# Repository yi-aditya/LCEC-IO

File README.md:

# LCEC-IO

Industrial EtherCAT slave I/O board: STM32F405VGT6 + LAN9252, 8 digital inputs, 12 MPG selector inputs, MPG encoder, 8 pluggable relay outputs, 2 × 0–10 V analog outputs. Designed in KiCad 10 with Claude Code.

- Specification: [docs/plan.md](docs/plan.md)
- Rules for Claude Code: [CLAUDE.md](CLAUDE.md)
- Cloud environment setup script: [scripts/cloud-setup.sh](scripts/cloud-setup.sh)

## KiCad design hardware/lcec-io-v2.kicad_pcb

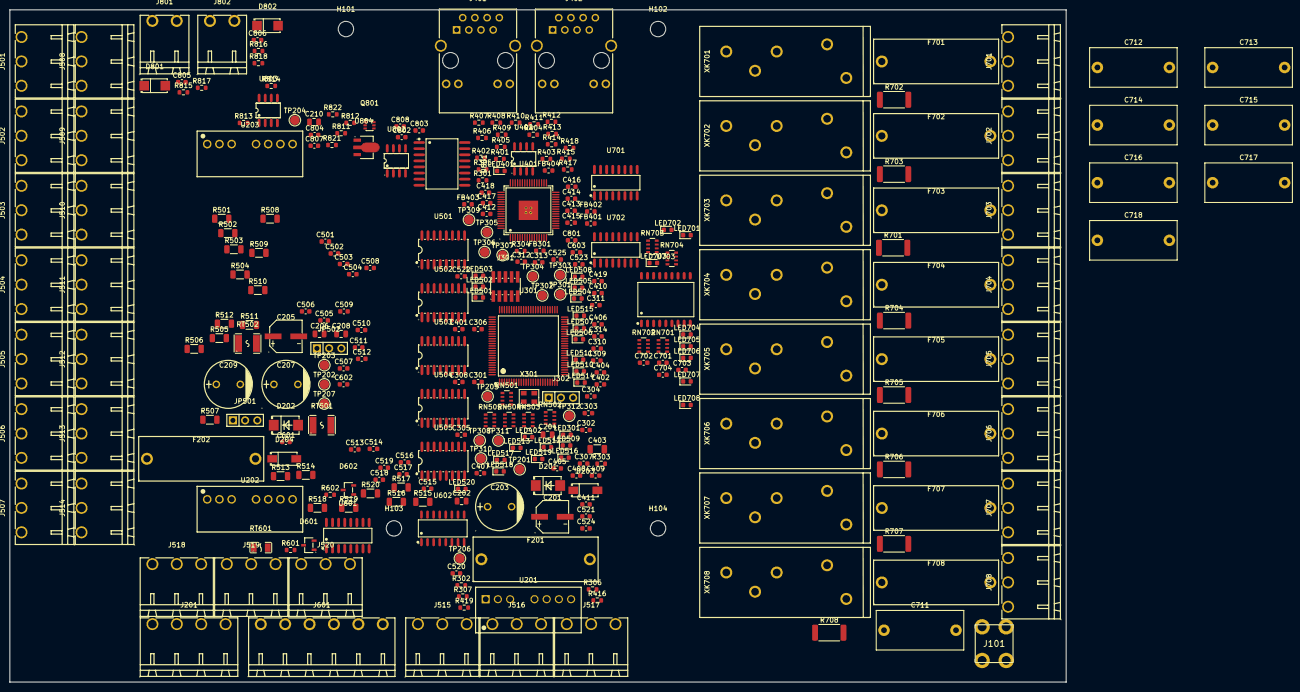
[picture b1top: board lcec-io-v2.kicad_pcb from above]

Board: 4 copper layers, 220.0 x 140.0 mm, 315 parts (0 on the bottom side), 249 nets, no tracks yet.

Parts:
C201, C205: 47uF 50V; CAP-SMD_BD6.3-L6.6-W6.6-LS7.2-FD
C202, C206: 1uF 50V; C_0805_2012Metric
C203, C207, C209: 100uF 100V; CAP-TH_BD10.0-P5.00-D0.6-FD
C204, C208, C210: 22uF 25V; C_0805_2012Metric
C301, C302, C303, C304, C305, C306, C307, C310, C313, C314, C404, C405, C406, C407, C408, C409, C410, C411, C412, C415, C416, C417, C418, C419, C521, C522, C523, C524, C525, C601, C602, C603, C701, C702, C703, C704, C801, C802, C803, C804: 100nF; C_0603_1608Metric
C308: 4.7uF; C_0603_1608Metric
C309, C413, C807, C808: 1uF; C_0603_1608Metric
C311, C312: 2.2uF; C_0603_1608Metric
C401, C402: 22nF 50V; C_0603_1608Metric
C403: 1nF 2kV; C_1206_3216Metric
C414: 470pF; C_0603_1608Metric
C501, C502, C503, C504, C505, C506, C507, C508, C509, C510, C511, C512, C513, C514, C515, C516, C517, C518, C519, C520, C805, C806: 10nF; C_0603_1608Metric
C711, C712, C713, C714, C715, C716, C717, C718: 47nF X2; C_Rect_L18.0mm_W8.0mm_P15.00mm_FKS3_FKP3
D201, D202: SMBJ30A; SMB_L4.4-W3.6-LS5.4-RD
D203, D204: SS54; SMA_L4.4-W2.8-LS5.4-R-RD
D601, D602: PSM712; SOT-23-3_L3.0-W1.7-P0.95-LS2.9-BR
D801, D802: SMAJ15A; SMA_L4.3-W2.6-LS5.2-RD
F201: 1 A 5x20; 64600001003
F202: 3 A 5x20; 64600001003
F701, F702, F703, F704, F705, F706, F707, F708: T5A 5x20; 64600001003
FB301: 600R@100MHz; L_0603_1608Metric
FB401, FB402, FB403, FB404: 220R@100MHz; L_0603_1608Metric
H101, H102, H103, H104: M3; MountingHole_3.2mm_M3
J101: PE; Keystone_7770_M3_PCB_Terminal
J201: 24 V entry; CONN-TH_4P-P5.08_KF2EDGR-5.08-4P
J301: SWD 2x5 1.27 mm; HDR-SMD_10P-P1.27-V-M-R2-C5-LS5.3
J302: USART2; HDR-TH_3P-P2.54-V-M_PZ254V-11-03P
J401, J402: HY911105AE; RJ45-TH_HR911105A
J501, J502, J503, J504, J505, J506, J507, J508, J509, J510, J511, J512, J513, J514, J515, J516, J517, J518, J519, J520: IN; CONN-TH_3P-P5.08_KF2EDGR-5.08-3P
J601: MPG; CONN-TH_6P-P5.08_KF2EDGR-5.08-6P
J701: DO1; CONN-TH_3P-P5.08_KF2EDGR-5.08-3P
J702: DO2; CONN-TH_3P-P5.08_KF2EDGR-5.08-3P
J703: DO3; CONN-TH_3P-P5.08_KF2EDGR-5.08-3P
J704: DO4; CONN-TH_3P-P5.08_KF2EDGR-5.08-3P
J705: DO5; CONN-TH_3P-P5.08_KF2EDGR-5.08-3P
J706: DO6; CONN-TH_3P-P5.08_KF2EDGR-5.08-3P
J707: DO7; CONN-TH_3P-P5.08_KF2EDGR-5.08-3P
J708: DO8; CONN-TH_3P-P5.08_KF2EDGR-5.08-3P
J801: AO1; CONN-TH_2P-P5.08_KF2EDGR-5.08-2P
J802: AO2; CONN-TH_2P-P5.08_KF2EDGR-5.08-2P
JP501, JP502: COM; HDR-TH_3P-P2.54-V-M_PZ254V-11-03P
LED301: heartbeat; LED_0603_1608Metric
LED401: RUN; LED_0603_1608Metric
LED402: ERR; LED_0603_1608Metric
LED501, LED502, LED503, LED504, LED505, LED506, LED507, LED508, LED509, LED510, LED511, LED512, LED513, LED514, LED515, LED516, LED517, LED518, LED519, LED520: IN; LED_0603_1608Metric
LED701, LED702, LED703, LED704, LED705, LED706, LED707, LED708: ON; LED_0603_1608Metric
Q801: 2N7002DW; SOT-363_L2.0-W1.3-P0.65-LS2.1-TL
R301, R302, R304, R305, R402, R403, R405: 10k; R_0603_1608Metric
R303, R401, R404, R406, R419, R811, R812: 1k; R_0603_1608Metric
R306, R307: 22R; R_0603_1608Metric
R407, R408, R409, R410, R411, R412, R413, R414: 49.9R; R_0603_1608Metric
R415: 12.1k 1%; R_0603_1608Metric
R416: 1M; R_0603_1608Metric
R417, R418: 4.7k; R_0603_1608Metric
R501, R502, R503, R504, R505, R506, R507, R508, R509, R510, R511, R512, R513, R514, R515, R516, R517, R518, R519, R520: 4.7k; R_1206_3216Metric
R601, R602: 120R; R_0603_1608Metric
R701, R702, R703, R704, R705, R706, R707, R708: 100R; R_2512_6332Metric
R813, R814: 10.0k 0.1%; R_0603_1608Metric
R815, R816: 100R; R_0603_1608Metric
R817, R818: 14.7k 0.1%; R_0603_1608Metric
R821, R822: 100k; R_0603_1608Metric
RN501, RN502, RN503, RN504, RN505: 4x1k; R_Array_Convex_4x0603
RN701, RN702: 4x22k; R_Array_Convex_4x0603
RN703, RN704: 4x100k; R_Array_Convex_4x0603
RT501, RT502: 0.5A PTC; F1812
RT601: 0.25A PTC; F1206
TP201: +24V_LOGIC; TestPoint_Pad_D2.0mm
TP202: +24V_IO; TestPoint_Pad_D2.0mm
TP203: +5V_IO; TestPoint_Pad_D2.0mm
TP204: +15V_A; TestPoint_Pad_D2.0mm
TP205: +3V3; TestPoint_Pad_D2.0mm
TP206: 0V_LOGIC; TestPoint_Pad_D2.0mm
TP207: 0V_IO; TestPoint_Pad_D2.0mm
TP301: ESC_SCK; TestPoint_Pad_D2.0mm
TP302: ESC_MISO; TestPoint_Pad_D2.0mm
TP303: ESC_MOSI; TestPoint_Pad_D2.0mm
TP304: ESC_CS; TestPoint_Pad_D2.0mm
TP305: DAC_SCK; TestPoint_Pad_D2.0mm
TP306: DAC_MOSI; TestPoint_Pad_D2.0mm
TP307: DAC_CS; TestPoint_Pad_D2.0mm
TP308: RELAY_OE; TestPoint_Pad_D2.0mm
TP309: AO_CLAMP; TestPoint_Pad_D2.0mm
TP310: MPG_A; TestPoint_Pad_D2.0mm
TP311: MPG_B; TestPoint_Pad_D2.0mm
TP312: PH1_TP; TestPoint_Pad_D2.0mm
U201: URB2403S-6WR3; PWRM-TH_URBXXXXS-6WR3_1
U202: URB2405S-6WR3; PWRM-TH_YLPTEC_URXXXXXS-6WR3
U203: URB2415S-6WR3; PWRM-TH_URBXXXXS-6WR3
U301: STM32F405VGT6; LQFP-100_L14.0-W14.0-P0.50-LS16.0-BL
U401: LAN9252I/PT; TQFP-64_L10.0-W10.0-P0.50-LS12.0-BL-EP
U402: 24LC32AT-I/SN; SOIC-8_L4.9-W3.9-P1.27-LS6.0-BL
U501, U502, U503, U504, U505: TLP290-4; SOP-16_L10.3-W4.4-P1.27-LS7.0-BL
U601: AM26LS32A; SOIC-16_L9.9-W3.9-P1.27-LS6.0-BL
U602: CA-IS3742LN; SOP-16_L10.0-W3.9-P1.27-LS6.0-BL
U701, U702: CA-IS3740LN; SOIC-16_L9.9-W3.9-P1.27-LS6.0-BL
U703: ULN2803A; SOP-18_L11.4-W7.6-P1.27-LS10.6-BL
U801: CA-IS3740HW; SOIC-16_L10.3-W7.5-P1.27-LS10.3-BL
U802: MCP4822-E/SN; SOIC-8_L4.9-W3.9-P1.27-LS6.0-BL
U803: LM2904; SOIC-8_L4.9-W3.9-P1.27-LS6.0-BL
U804: L78L05; SOT-89-3_L4.5-W2.5-P1.50-LS4.2-TL
X301: 25 MHz; OSC-SMD_4P-L3.2-W2.5-BL_KYOCERA_KC3225A
XK701, XK702, XK703, XK704, XK705, XK706, XK707, XK708: P2R-05P; RELAY-TH_P2R-05P

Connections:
0V_IO: C205.2, C206.2, C207.2, C208.2, C209.2, C601.2, C602.2, C702.2, C704.2, D202.2, D601.3, D602.3, J201.4, J501.3, J502.3, J503.3, J504.3, J505.3, J506.3, J507.3, J508.3, J509.3, J510.3, J511.3, J512.3, J513.3, J514.3, J515.3, J516.3, J517.3, J518.3, J519.3, J520.3, J601.2, JP501.3, JP502.3, RN703.1, RN703.2, RN703.3, RN703.4, RN704.1, RN704.2, RN704.3, RN704.4, TP207.1, U202.1, U202.7, U203.1, U601.8, U601.9, U601.10, U601.12, U601.14, U601.15, U602.9, U602.15, U701.9, U701.15, U702.9, U702.15, U703.9
0V_LOGIC: C201.2, C202.2, C203.2, D201.2, J201.2, TP206.1, U201.1
+3V3: C204.1, C301.1, C302.1, C303.1, C304.1, C305.1, C306.1, C307.1, C308.1, C314.1, C404.1, C405.1, C406.1, C407.1, C408.1, C409.1, C419.1, C521.1, C522.1, C523.1, C524.1, C525.1, C603.1, C701.1, C703.1, C801.1, FB301.1, FB401.1, FB402.1, FB403.1, J301.1, R304.1, R305.1, R401.1, R402.1, R417.1, R418.1, RN501.1, RN501.2, RN501.3, RN501.4, RN502.1, RN502.2, RN502.3, RN502.4, RN503.1, RN503.2, RN503.3, RN503.4, RN504.1, RN504.2, RN504.3, RN504.4, RN505.1, RN505.2, RN505.3, RN505.4, TP205.1, U201.6, U301.6, U301.11, U301.19, U301.28, U301.50, U301.75, U301.100, U401.5, U401.7, U401.14, U401.20, U401.32, U401.37, U401.47, U402.8, U602.1, U602.7, U701.1, U702.1, U801.1, X301.1, X301.4
+3V3_BIAS: C412.1, FB403.2, U401.58
+3V3_TXRX1: C401.1, C410.1, FB401.2, J401.4, J401.5, R407.1, R408.1, R409.1, R410.1, U401.51
+3V3_TXRX2: C402.1, C411.1, FB402.2, J402.4, J402.5, R411.1, R412.1, R413.1, R414.1, U401.64
+5V_A: C802.1, C803.1, C808.1, U801.10, U801.16, U802.1, U804.1
+5V_IO: C208.1, C601.1, C602.1, C702.1, C704.1, RT601.2, TP203.1, U202.6, U601.4, U601.16, U602.10, U602.16, U701.16, U702.16
+15V_A: C210.1, C804.1, C807.1, TP204.1, U203.6, U803.8, U804.3
+24V_IO: C205.1, C206.1, C207.1, C209.1, D202.1, D204.2, JP501.1, JP502.1, RN701.5, RN701.6, RN701.7, RN701.8, RN702.5, RN702.6, RN702.7, RN702.8, RT501.1, RT502.1, TP202.1, U202.2, U203.2, U703.10, XK701.1, XK702.1, XK703.1, XK704.1, XK705.1, XK706.1, XK707.1, XK708.1
+24V_LOGIC: C201.1, C202.1, C203.1, D201.1, D203.2, TP201.1, U201.2
/Analog/AO1_P: Q801.3, R811.2, R821.1, U803.3
/Analog/AO2_P: Q801.6, R812.2, R822.1, U803.5
/Analog/CLAMP_A: Q801.2, Q801.5, U801.11
/Analog/CS_A: U801.12, U802.2
/Analog/DAC_A: R811.1, U802.8
/Analog/DAC_B: R812.1, U802.6
/Analog/SCK_A: U801.14, U802.3
/Analog/SDI_A: U801.13, U802.4
/EtherCAT/CLK_ESC: R307.2, U401.1
/EtherCAT/EESCL: R417.2, U401.43, U402.6
/EtherCAT/EESDA: R418.2, U401.42, U402.5
/EtherCAT/ERR_LED: R419.1, U301.84
/EtherCAT/ESC_IRQ: U301.33, U401.44
/EtherCAT/ESC_RST: R304.2, U301.34, U401.11
/EtherCAT/ESC_SYNC0: U301.23, U401.34
/EtherCAT/ESC_SYNC1: U301.7, U401.18
/EtherCAT/LNK_ACT0: J401.9, R406.1
/EtherCAT/LNK_ACT1: J402.9, R404.1
/EtherCAT/SHIELD: C403.1, J401.8, J401.SH1, J401.SH2, J402.8, J402.SH1, J402.SH2, R416.1
/EtherCAT/VDD12TX: C417.1, C418.1, FB404.2, U401.56, U401.59
/EtherCAT/VDDCR: C413.1, C414.1, C415.1, C416.1, FB404.1, U401.6, U401.24, U401.38
/Inputs/COM_DI: C501.2, C502.2, C503.2, C504.2, C505.2, C506.2, C507.2, C508.2, JP501.2, U501.2, U501.4, U501.6, U501.8, U502.2, U502.4, U502.6, U502.8
/Inputs/COM_SEL: C509.2, C510.2, C511.2, C512.2, C513.2, C514.2, C515.2, C516.2, C517.2, C518.2, C519.2, C520.2, JP502.2, U503.2, U503.4, U503.6, U503.8, U504.2, U504.4, U504.6, U504.8, U505.2, U505.4, U505.6, U505.8
/Inputs/DI1: LED501.1, U301.15, U501.16
/Inputs/DI1-4/LA1: LED501.2, RN501.5
/Inputs/DI1-4/LA2: LED502.2, RN501.6
/Inputs/DI1-4/LA3: LED503.2, RN501.7
/Inputs/DI1-4/LA4: LED504.2, RN501.8
/Inputs/DI2: LED502.1, U301.16, U501.14
/Inputs/DI3: LED503.1, U301.17, U501.12
/Inputs/DI4: LED504.1, U301.18, U501.10
/Inputs/DI5: LED505.1, U301.63, U502.16
/Inputs/DI5-8/LA1: LED505.2, RN502.5
/Inputs/DI5-8/LA2: LED506.2, RN502.6
/Inputs/DI5-8/LA3: LED507.2, RN502.7
/Inputs/DI5-8/LA4: LED508.2, RN502.8
/Inputs/DI6: LED506.1, U301.64, U502.14
/Inputs/DI7: LED507.1, U301.65, U502.12
/Inputs/DI8: LED508.1, U301.66, U502.10
/Inputs/SEL1: LED509.1, U301.35, U503.16
/Inputs/SEL1-4/LA1: LED509.2, RN503.5
/Inputs/SEL1-4/LA2: LED510.2, RN503.6
/Inputs/SEL1-4/LA3: LED511.2, RN503.7
/Inputs/SEL1-4/LA4: LED512.2, RN503.8
/Inputs/SEL2: LED510.1, U301.36, U503.14
/Inputs/SEL3: LED511.1, U301.37, U503.12
/Inputs/SEL4: LED512.1, U301.95, U503.10
/Inputs/SEL5: LED513.1, U301.96, U504.16
/Inputs/SEL5-8/LA1: LED513.2, RN504.5
/Inputs/SEL5-8/LA2: LED514.2, RN504.6
/Inputs/SEL5-8/LA3: LED515.2, RN504.7
/Inputs/SEL5-8/LA4: LED516.2, RN504.8
/Inputs/SEL6: LED514.1, U301.47, U504.14
/Inputs/SEL7: LED515.1, U301.48, U504.12
/Inputs/SEL8: LED516.1, U301.77, U504.10
/Inputs/SEL9: LED517.1, U301.92, U505.16
/Inputs/SEL9-12/LA1: LED517.2, RN505.5
/Inputs/SEL9-12/LA2: LED518.2, RN505.6
/Inputs/SEL9-12/LA3: LED519.2, RN505.7
/Inputs/SEL9-12/LA4: LED520.2, RN505.8
/Inputs/SEL10: LED518.1, U301.93, U505.14
/Inputs/SEL11: LED519.1, U301.8, U505.12
/Inputs/SEL12: LED520.1, U301.9, U505.10
/Inputs/SENSE_DI: J501.1, J502.1, J503.1, J504.1, J505.1, J506.1, J507.1, J508.1, RT501.2
/Inputs/SENSE_SEL: J509.1, J510.1, J511.1, J512.1, J513.1, J514.1, J515.1, J516.1, J517.1, J518.1, J519.1, J520.1, RT502.2
/MCU/AO_CLAMP: R305.2, TP309.1, U301.53, U801.6
/MCU/BOOT0: R301.1, U301.94
/MCU/CLK_MCU: R306.2, U301.12
/MCU/DAC_CS: TP307.1, U301.51, U801.5
/MCU/DAC_MOSI: TP306.1, U301.54, U801.4
/MCU/DAC_SCK: TP305.1, U301.52, U801.3
/MCU/DO1: U301.67, U701.3
/MCU/DO2: U301.68, U701.4
/MCU/DO3: U301.69, U701.5
/MCU/DO4: U301.70, U701.6
/MCU/DO5: U301.71, U702.3
/MCU/DO6: U301.78, U702.4
/MCU/DO7: U301.79, U702.5
/MCU/DO8: U301.80, U702.6
/MCU/ESC_CS: TP304.1, U301.29, U401.50
/MCU/ESC_MISO: TP302.1, U301.31, U401.13
/MCU/ESC_MOSI: TP303.1, U301.32, U401.17
/MCU/ESC_SCK: TP301.1, U301.30, U401.19
/MCU/HB_LED: R303.1, U301.24
/MCU/MPG_A: TP310.1, U301.90, U602.5
/MCU/MPG_B: TP311.1, U301.91, U602.6
/MCU/NRST: C313.1, J301.10, U301.14
/MCU/PH1_TP: TP312.1, U301.13
/MCU/RELAY_OE: R302.1, TP308.1, U301.83, U602.3
/MCU/SWCLK: J301.4, U301.76
/MCU/SWDIO: J301.2, U301.72
/MCU/SWO: J301.6, U301.89
/MCU/UART2_RX: J302.2, U301.26
/MCU/UART2_TX: J302.1, U301.25
/MCU/VDDA: C309.1, C310.1, FB301.2, U301.21, U301.22
/MPG/ENC_A_N: D601.2, J601.4, R601.2, U601.1
/MPG/ENC_A_P: D601.1, J601.3, R601.1, U601.2
/MPG/ENC_A_R: U601.3, U602.12
/MPG/ENC_B_N: D602.2, J601.6, R602.2, U601.7
/MPG/ENC_B_P: D602.1, J601.5, R602.1, U601.6
/MPG/ENC_B_R: U601.5, U602.11
/OE_FIELD: U602.14, U701.10, U702.10
/Power/24V_IO_IN: F202.1, J201.3
/Power/24V_LOGIC_IN: F201.1, J201.1
/Relays/DRV1: LED701.1, U703.18, XK701.5
/Relays/DRV2: LED702.1, U703.17, XK702.5
/Relays/DRV3: LED703.1, U703.16, XK703.5
/Relays/DRV4: LED704.1, U703.15, XK704.5
/Relays/DRV5: LED705.1, U703.14, XK705.5
/Relays/DRV6: LED706.1, U703.13, XK706.5
/Relays/DRV7: LED707.1, U703.12, XK707.5
/Relays/DRV8: LED708.1, U703.11, XK708.5
/Relays/IN1: RN703.5, U701.14, U703.1
/Relays/IN2: RN703.6, U701.13, U703.2
/Relays/IN3: RN703.7, U701.12, U703.3
/Relays/IN4: RN703.8, U701.11, U703.4
/Relays/IN5: RN704.5, U702.14, U703.5
/Relays/IN6: RN704.6, U702.13, U703.6
/Relays/IN7: RN704.7, U702.12, U703.7
/Relays/IN8: RN704.8, U702.11, U703.8
/Relays/LR1: LED701.2, RN701.4
/Relays/LR2: LED702.2, RN701.3
/Relays/LR3: LED703.2, RN701.2
/Relays/LR4: LED704.2, RN701.1
/Relays/LR5: LED705.2, RN702.4
/Relays/LR6: LED706.2, RN702.3
/Relays/LR7: LED707.2, RN702.2
/Relays/LR8: LED708.2, RN702.1
AGND: C210.2, C802.2, C803.2, C804.2, C805.2, C806.2, C807.2, C808.2, D801.2, D802.2, J801.2, J802.2, Q801.1, Q801.4, R813.2, R814.2, R821.2, R822.2, U203.7, U801.9, U801.15, U802.5, U802.7, U803.4, U804.2
GND_L: C204.2, C301.2, C302.2, C303.2, C304.2, C305.2, C306.2, C307.2, C308.2, C309.2, C310.2, C311.2, C312.2, C313.2, C314.2, C401.2, C402.2, C404.2, C405.2, C406.2, C407.2, C408.2, C409.2, C410.2, C411.2, C412.2, C413.2, C414.2, C415.2, C416.2, C417.2, C418.2, C419.2, C521.2, C522.2, C523.2, C524.2, C525.2, C603.2, C701.2, C703.2, C801.2, J301.3, J301.5, J301.9, J302.3, J401.10, J402.10, LED301.1, LED402.1, R301.2, R302.2, R403.2, R405.2, R415.2, U201.7, U301.10, U301.20, U301.27, U301.74, U301.99, U401.4, U401.8, U401.9, U401.10, U401.41, U401.65, U402.1, U402.2, U402.3, U402.4, U402.7, U501.9, U501.11, U501.13, U501.15, U502.9, U502.11, U502.13, U502.15, U503.9, U503.11, U503.13, U503.15, U504.9, U504.11, U504.13, U504.15, U505.9, U505.11, U505.13, U505.15, U602.2, U602.4, U602.8, U701.2, U701.8, U702.2, U702.8, U801.2, U801.8, X301.2
unnamed: C711.1, R701.2
unnamed: C712.1, R702.2
unnamed: C713.1, R703.2
unnamed: C714.1, R704.2
unnamed: C715.1, R705.2
unnamed: C716.1, R706.2
unnamed: C717.1, R707.2
unnamed: C718.1, R708.2
unnamed: D203.1, F201.2
unnamed: D204.1, F202.2
unnamed: C805.1, D801.1, J801.1, R815.2, R817.2
unnamed: C806.1, D802.1, J802.1, R816.2, R818.2
unnamed: F701.2, J701.1
unnamed: F702.2, J702.1
unnamed: F703.2, J703.1
unnamed: F704.2, J704.1
unnamed: F705.2, J705.1
unnamed: F706.2, J706.1
unnamed: F707.2, J707.1
unnamed: F708.2, J708.1
unnamed: J401.3, R409.2, U401.55
unnamed: J401.6, R410.2, U401.54
unnamed: J401.1, R407.2, U401.53
unnamed: J401.2, R408.2, U401.52
unnamed: J402.3, R413.2, U401.60
unnamed: J402.6, R414.2, U401.61
unnamed: J402.1, R411.2, U401.62
unnamed: J402.2, R412.2, U401.63
unnamed: J501.2, R501.1
unnamed: J502.2, R502.1
unnamed: J503.2, R503.1
unnamed: J504.2, R504.1
unnamed: J505.2, R505.1
unnamed: J506.2, R506.1
unnamed: J507.2, R507.1
unnamed: J508.2, R508.1
unnamed: J509.2, R509.1
unnamed: J510.2, R510.1
unnamed: J511.2, R511.1
unnamed: J512.2, R512.1
unnamed: J513.2, R513.1
unnamed: J514.2, R514.1
unnamed: J515.2, R515.1
unnamed: J516.2, R516.1
unnamed: J517.2, R517.1
unnamed: J518.2, R518.1
unnamed: J519.2, R519.1
unnamed: J520.2, R520.1
unnamed: J601.1, RT601.1
unnamed: LED301.2, R303.2
unnamed: LED401.2, R401.2
unnamed: LED401.1, R402.2, U401.45
unnamed: LED402.2, R419.2
unnamed: C311.1, U301.49
unnamed: C312.1, U301.73
unnamed: R405.1, R406.2, U401.48
unnamed: R403.1, R404.2, U401.46
unnamed: R415.1, U401.57
unnamed: C501.1, R501.2, U501.1
unnamed: C502.1, R502.2, U501.3
unnamed: C503.1, R503.2, U501.5
unnamed: C504.1, R504.2, U501.7
unnamed: C505.1, R505.2, U502.1
unnamed: C506.1, R506.2, U502.3
unnamed: C507.1, R507.2, U502.5
unnamed: C508.1, R508.2, U502.7
unnamed: C509.1, R509.2, U503.1
unnamed: C510.1, R510.2, U503.3
unnamed: C511.1, R511.2, U503.5
unnamed: C512.1, R512.2, U503.7
unnamed: C513.1, R513.2, U504.1
unnamed: C514.1, R514.2, U504.3
unnamed: C515.1, R515.2, U504.5
unnamed: C516.1, R516.2, U504.7
unnamed: C517.1, R517.2, U505.1
unnamed: C518.1, R518.2, U505.3
unnamed: C519.1, R519.2, U505.5
unnamed: C520.1, R520.2, U505.7
unnamed: R813.1, R817.1, U803.2
unnamed: R815.1, U803.1
unnamed: R814.1, R818.1, U803.6
unnamed: R816.1, U803.7
unnamed: R306.1, R307.1, X301.3
unnamed: F701.1, R701.1, XK701.2
unnamed: J701.3, XK701.4
unnamed: C711.2, J701.2, XK701.3
unnamed: F702.1, R702.1, XK702.2
unnamed: J702.3, XK702.4
unnamed: C712.2, J702.2, XK702.3
unnamed: F703.1, R703.1, XK703.2
unnamed: J703.3, XK703.4
unnamed: C713.2, J703.2, XK703.3
unnamed: F704.1, R704.1, XK704.2
unnamed: J704.3, XK704.4
unnamed: C714.2, J704.2, XK704.3
unnamed: F705.1, R705.1, XK705.2
unnamed: J705.3, XK705.4
unnamed: C715.2, J705.2, XK705.3
unnamed: F706.1, R706.1, XK706.2
unnamed: J706.3, XK706.4
unnamed: C716.2, J706.2, XK706.3
unnamed: F707.1, R707.1, XK707.2
unnamed: J707.3, XK707.4
unnamed: C717.2, J707.2, XK707.3
unnamed: F708.1, R708.1, XK708.2
unnamed: J708.3, XK708.4
unnamed: C718.2, J708.2, XK708.3
PE: C403.2, J101.1, R416.2

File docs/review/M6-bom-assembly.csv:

Refs,Qty,Value,Footprint,LCSC,MPN,Manufacturer
"C201,C205",2,47uF 50V,lcsc:CAP-SMD_BD6.3-L6.6-W6.6-LS7.2-FD,C970679,RVT1H470M0607 47UF 50V,DMBJ
"C202,C206",2,1uF 50V,Capacitor_SMD:C_0805_2012Metric,C91185,CC0805KKX7R9BB105,YAGEO
"C203,C207,C209",3,100uF 100V,lcsc:CAP-TH_BD10.0-P5.00-D0.6-FD,C2960285,100V100uF CD288,HRK
"C204,C208,C210",3,22uF 25V,Capacitor_SMD:C_0805_2012Metric,C45783,CL21A226MAQNNNE,Samsung Electro-Mechanics
"C301,C302,C303,C304,C305,C306,C307,C310,C313,C314,C404,C405,C406,C407,C408,C409,C410,C411,C412,C415,C416,C417,C418,C419,C521,C522,C523,C524,C525,C601,C602,C603,C701,C702,C703,C704,C801,C802,C803,C804",40,100nF,Capacitor_SMD:C_0603_1608Metric,C1591,CL10B104KB8NNNC,Samsung Electro-Mechanics
C308,1,4.7uF,Capacitor_SMD:C_0603_1608Metric,C19666,CL10A475KO8NNNC,Samsung Electro-Mechanics
"C309,C413,C807,C808",4,1uF,Capacitor_SMD:C_0603_1608Metric,C559769,CC0603KRX7R9BB105,YAGEO
"C311,C312",2,2.2uF,Capacitor_SMD:C_0603_1608Metric,C23630,CL10A225KO8NNNC,Samsung Electro-Mechanics
"C401,C402",2,22nF 50V,Capacitor_SMD:C_0603_1608Metric,C106222,CC0603KRX7R9BB223,YAGEO
C403,1,1nF 2kV,Capacitor_SMD:C_1206_3216Metric,C9196,1206B102K202NT,FH
C414,1,470pF,Capacitor_SMD:C_0603_1608Metric,C1620,0603B471K500NT,FH
"C501,C502,C503,C504,C505,C506,C507,C508,C509,C510,C511,C512,C513,C514,C515,C516,C517,C518,C519,C520,C805,C806",22,10nF,Capacitor_SMD:C_0603_1608Metric,C1589,CL10B103KB8NNNC,Samsung Electro-Mechanics
"D201,D202",2,SMBJ30A,lcsc:SMB_L4.4-W3.6-LS5.4-RD,C83851,SMBJ30A,Littelfuse
"D203,D204",2,SS54,lcsc:SMA_L4.4-W2.8-LS5.4-R-RD,C22452,SS54,MDD(Microdiode Semiconductor)
"D601,D602",2,PSM712,lcsc:SOT-23-3_L3.0-W1.7-P0.95-LS2.9-BR,C32677,PSM712-LF-T7,PROTEK
"D801,D802",2,SMAJ15A,lcsc:SMA_L4.3-W2.6-LS5.2-RD,C148216,SMAJ15A,Littelfuse
F201,1,1 A 5x20,lcsc:64600001003,C206887,64600001003,Littelfuse
F202,1,3 A 5x20,lcsc:64600001003,C206887,64600001003,Littelfuse
FB301,1,600R@100MHz,Inductor_SMD:L_0603_1608Metric,C19330,BLM18AG601SN1D,muRata
"FB401,FB402,FB403,FB404",4,220R@100MHz,Inductor_SMD:L_0603_1608Metric,C85827,BLM18EG221SN1D,muRata
"F701,F702,F703,F704,F705,F706,F707,F708",8,T5A 5x20,lcsc:64600001003,C206887,64600001003,Littelfuse
J101,1,PE,lcsc:Keystone_7770_M3_PCB_Terminal,C5272782,7770,Keystone
J201,1,24 V entry,lcsc:CONN-TH_4P-P5.08_KF2EDGR-5.08-4P,C441206,KF2EDGR-5.08-4P,Cixi Kefa Elec
J301,1,SWD 2x5 1.27 mm,lcsc:HDR-SMD_10P-P1.27-V-M-R2-C5-LS5.3,C3975188,PZ127-2-05-S,HCTL
J302,1,USART2,lcsc:HDR-TH_3P-P2.54-V-M_PZ254V-11-03P,C2937625,PZ254V-11-03P,XFCN
"J401,J402",2,HY911105AE,lcsc:RJ45-TH_HR911105A,C69427,HY911105AE,HANRUN(Zhongshan HanRun Elec)
"J501,J502,J503,J504,J505,J506,J507,J508,J509,J510,J511,J512,J513,J514,J515,J516,J517,J518,J519,J520",20,IN,lcsc:CONN-TH_3P-P5.08_KF2EDGR-5.08-3P,C441205,KF2EDGR-5.08-3P,Cixi Kefa Elec
"JP501,JP502",2,COM,lcsc:HDR-TH_3P-P2.54-V-M_PZ254V-11-03P,C2937625,PZ254V-11-03P,XFCN
J601,1,MPG,lcsc:CONN-TH_6P-P5.08_KF2EDGR-5.08-6P,C441208,KF2EDGR-5.08-6P,Cixi Kefa Elec
J701,1,DO1,lcsc:CONN-TH_3P-P5.08_KF2EDGR-5.08-3P,C441205,KF2EDGR-5.08-3P,Cixi Kefa Elec
J702,1,DO2,lcsc:CONN-TH_3P-P5.08_KF2EDGR-5.08-3P,C441205,KF2EDGR-5.08-3P,Cixi Kefa Elec
J703,1,DO3,lcsc:CONN-TH_3P-P5.08_KF2EDGR-5.08-3P,C441205,KF2EDGR-5.08-3P,Cixi Kefa Elec
J704,1,DO4,lcsc:CONN-TH_3P-P5.08_KF2EDGR-5.08-3P,C441205,KF2EDGR-5.08-3P,Cixi Kefa Elec
J705,1,DO5,lcsc:CONN-TH_3P-P5.08_KF2EDGR-5.08-3P,C441205,KF2EDGR-5.08-3P,Cixi Kefa Elec
J706,1,DO6,lcsc:CONN-TH_3P-P5.08_KF2EDGR-5.08-3P,C441205,KF2EDGR-5.08-3P,Cixi Kefa Elec
J707,1,DO7,lcsc:CONN-TH_3P-P5.08_KF2EDGR-5.08-3P,C441205,KF2EDGR-5.08-3P,Cixi Kefa Elec
J708,1,DO8,lcsc:CONN-TH_3P-P5.08_KF2EDGR-5.08-3P,C441205,KF2EDGR-5.08-3P,Cixi Kefa Elec
J801,1,AO1,lcsc:CONN-TH_2P-P5.08_KF2EDGR-5.08-2P,C441204,KF2EDGR-5.08-2P,Cixi Kefa Elec
J802,1,AO2,lcsc:CONN-TH_2P-P5.08_KF2EDGR-5.08-2P,C441204,KF2EDGR-5.08-2P,Cixi Kefa Elec
LED301,1,heartbeat,LED_SMD:LED_0603_1608Metric,C2287,KT-0603Y,Hubei KENTO Elec
LED401,1,RUN,LED_SMD:LED_0603_1608Metric,C89809,NCD0603C3,NATIONSTAR
LED402,1,ERR,LED_SMD:LED_0603_1608Metric,C2286,KT-0603R,Hubei KENTO Elec
"LED501,LED502,LED503,LED504,LED505,LED506,LED507,LED508,LED509,LED510,LED511,LED512,LED513,LED514,LED515,LED516,LED517,LED518,LED519,LED520",20,IN,LED_SMD:LED_0603_1608Metric,C89809,NCD0603C3,NATIONSTAR
"LED701,LED702,LED703,LED704,LED705,LED706,LED707,LED708",8,ON,LED_SMD:LED_0603_1608Metric,C89809,NCD0603C3,NATIONSTAR
Q801,1,2N7002DW,lcsc:SOT-363_L2.0-W1.3-P0.65-LS2.1-TL,C83571,2N7002DW-7-F,DIODES
"R301,R302,R304,R305,R402,R403,R405",7,10k,Resistor_SMD:R_0603_1608Metric,C25804,0603WAF1002T5E,UNI-ROYAL
"R303,R401,R404,R406,R419,R811,R812",7,1k,Resistor_SMD:R_0603_1608Metric,C21190,0603WAF1001T5E,UNI-ROYAL
"R306,R307",2,22R,Resistor_SMD:R_0603_1608Metric,C23345,0603WAF220JT5E,UNI-ROYAL
"R407,R408,R409,R410,R411,R412,R413,R414",8,49.9R,Resistor_SMD:R_0603_1608Metric,C23185,0603WAF499JT5E,UNI-ROYAL
R415,1,12.1k 1%,Resistor_SMD:R_0603_1608Metric,C22864,0603WAF1212T5E,UNI-ROYAL
R416,1,1M,Resistor_SMD:R_0603_1608Metric,C22935,0603WAF1004T5E,UNI-ROYAL
"R417,R418",2,4.7k,Resistor_SMD:R_0603_1608Metric,C23162,0603WAF4701T5E,UNI-ROYAL
"R501,R502,R503,R504,R505,R506,R507,R508,R509,R510,R511,R512,R513,R514,R515,R516,R517,R518,R519,R520",20,4.7k,Resistor_SMD:R_1206_3216Metric,C17936,1206W4F4701T5E,UNI-ROYAL
"RN501,RN502,RN503,RN504,RN505",5,4x1k,Resistor_SMD:R_Array_Convex_4x0603,C20197,4D03WGJ0102T5E,UNI-ROYAL
"RT501,RT502",2,0.5A PTC,lcsc:F1812,C151168,1812L050/30PR,Littelfuse
RT601,1,0.25A PTC,lcsc:F1206,C70068,nSMD025,TECHFUSE
"RN701,RN702",2,4x22k,Resistor_SMD:R_Array_Convex_4x0603,C25729,4D03WGJ0223T5E,UNI-ROYAL
"RN703,RN704",2,4x100k,Resistor_SMD:R_Array_Convex_4x0603,C1996,4D03WGJ0104T5E,UNI-ROYAL
"R813,R814",2,10.0k 0.1%,Resistor_SMD:R_0603_1608Metric,C95204,RT0603BRD0710KL,YAGEO
"R815,R816",2,100R,Resistor_SMD:R_0603_1608Metric,C22775,0603WAF1000T5E,UNI-ROYAL
"R817,R818",2,14.7k 0.1%,Resistor_SMD:R_0603_1608Metric,C705725,RT0603BRD0714K7L,YAGEO
"R821,R822",2,100k,Resistor_SMD:R_0603_1608Metric,C25803,0603WAF1003T5E,UNI-ROYAL
U201,1,URB2403S-6WR3,lcsc:PWRM-TH_URBXXXXS-6WR3_1,C5369843,URB2403S-6WR3,YLPTEC
U202,1,URB2405S-6WR3,lcsc:PWRM-TH_YLPTEC_URXXXXXS-6WR3,C3031185,URB2405S-6WR3,YLPTEC
U203,1,URB2415S-6WR3,lcsc:PWRM-TH_URBXXXXS-6WR3,C5369844,URB2415S-6WR3,YLPTEC
U301,1,STM32F405VGT6,lcsc:LQFP-100_L14.0-W14.0-P0.50-LS16.0-BL,C56621,STM32F405VGT6,ST
U401,1,LAN9252I/PT,lcsc:TQFP-64_L10.0-W10.0-P0.50-LS12.0-BL-EP,C80933,LAN9252I/PT,MICROCHIP
U402,1,24LC32AT-I/SN,lcsc:SOIC-8_L4.9-W3.9-P1.27-LS6.0-BL,C615715,24LC32AT-I/SN,MICROCHIP
"U501,U502,U503,U504,U505",5,TLP290-4,lcsc:SOP-16_L10.3-W4.4-P1.27-LS7.0-BL,C39031,"TLP290-4(GB-TP,E",TOSHIBA
U601,1,AM26LS32A,lcsc:SOIC-16_L9.9-W3.9-P1.27-LS6.0-BL,C6180,AM26LS32ACDR,TI
U602,1,CA-IS3742LN,lcsc:SOP-16_L10.0-W3.9-P1.27-LS6.0-BL,C5347249,CA-IS3742LN,Chipanalog
"U701,U702",2,CA-IS3740LN,lcsc:SOIC-16_L9.9-W3.9-P1.27-LS6.0-BL,C428888,CA-IS3740LN,Chipanalog
U703,1,ULN2803A,lcsc:SOP-18_L11.4-W7.6-P1.27-LS10.6-BL,C845537,ULN2803A,UMW
U801,1,CA-IS3740HW,lcsc:SOIC-16_L10.3-W7.5-P1.27-LS10.3-BL,C528653,CA-IS3740HW,Chipanalog
U802,1,MCP4822-E/SN,lcsc:SOIC-8_L4.9-W3.9-P1.27-LS6.0-BL,C16040,MCP4822-E/SN,MICROCHIP
U803,1,LM2904,lcsc:SOIC-8_L4.9-W3.9-P1.27-LS6.0-BL,C7934,LM2904DR,TI
U804,1,L78L05,lcsc:SOT-89-3_L4.5-W2.5-P1.50-LS4.2-TL,C42738,L78L05ABUTR,ST
X301,1,25 MHz,lcsc:OSC-SMD_4P-L3.2-W2.5-BL_KYOCERA_KC3225A,C2595919,ECS-3225MVQ-250-CN-TR,ECS
"XK701,XK702,XK703,XK704,XK705,XK706,XK707,XK708",8,P2R-05P,lcsc:RELAY-TH_P2R-05P,C1524860,P2R-05P,OMRON

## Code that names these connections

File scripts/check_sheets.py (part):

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        if f == "lan9252 spi":
            for p in pins.split(","):
                pin, role = p.split()
                exp[{"SCK": "ESC_SCK", "MISO": "ESC_MISO", "MOSI": "ESC_MOSI", "CS": "ESC_CS"}[role]] = pin
        elif f == "lan9252 irq":
            exp["ESC_IRQ"] = pins
        elif f.startswith("lan9252 sync0"):
            exp["ESC_SYNC0"], exp["ESC_SYNC1"] = [p.strip() for p in pins.split("/")]
        elif f.startswith("lan9252 rst"):
            exp["ESC_RST"] = pins
        elif f == "dac spi":
            for p in pins.split(","):
                pin, role = p.split()
                exp[{"SCK": "DAC_SCK", "MOSI": "DAC_MOSI", "CS": "DAC_CS"}[role]] = pin
        elif f == "ao_clamp":
            exp["AO_CLAMP"] = pins
        elif f.startswith("mpg a"):
            exp["MPG_A"], exp["MPG_B"] = [p.strip() for p in pins.split("/")]
        elif f.startswith("di1"):
            for i, p in enumerate(expand(pins)):
                exp[f"DI{i + 1}"] = p
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            for i, p in enumerate(expand(pins)):
                exp[f"DO{i + 1}"] = p
        elif f == "relay oe":
            exp["RELAY_OE"] = pins
        elif f == "heartbeat led":
            exp["HB_LED"] = pins
        elif f == "ethercat err led":
            exp["ERR_LED"] = pins
        elif f == "debug":
            m = re.findall(r"(PA13) SWDIO, (PA14) SWCLK, (PB3) SWO, (PA2)/(PA3) USART2", pins)[0]
            exp.update(SWDIO=m[0], SWCLK=m[1], SWO=m[2], UART2_TX=m[3], UART2_RX=m[4])
        elif f == "clock":
            exp["CLK_MCU"] = pins
        elif f == "spare":
            exp["PH1_TP"] = pins
    return exp


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
    stm = {v[0]: str(k) for k, v in T["C56621"]["pins"].items()}
    # 1. nets that cross from the STM32 to the LAN9252 (through the root sheet and the hierarchical labels)
    for esc, lan, mcu_pin in (("ESC_CS", "50", "PA4"), ("ESC_SCK", "19", "PA5"), ("ESC_MISO", "13", "PA6"), ("ESC_MOSI", "17", "PA7"),
                              ("ESC_IRQ", "44", "PC4"), ("ESC_SYNC0", "34", "PA0"), ("ESC_SYNC1", "18", "PC13"), ("ESC_RST", "11", "PC5")):
        a, b = net(pinnet, "U301", stm[mcu_pin]), net(pinnet, "U401", lan)
        if a != b:
            fail(f"STM32 {mcu_pin} ({a}) is not on the same net as LAN9252 pin {lan} ({b}) for {esc}")
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        need("GND_L", net(pinnet, "U401", pin), "10k")      # chip mode 00
    need("GND_L", net(pinnet, "U401", "57"), "12.1k 1%")    # RBIAS
    # 3. link LEDs and RUN LED
    for chip_pin, jack, lnk in (("48", "J401", "LNK_ACT0"), ("46", "J402", "LNK_ACT1")):
        need(lnk, net(pinnet, "U401", chip_pin), "1k")
        want(jack, "9", lnk)
        want(jack, "10", "GND_L")
    want("LED401", "1", net(pinnet, "U401", "45"))
    need("+3V3", net(pinnet, "LED401", "2"), "1k")
    # 4. magnetics: each line to its jack pin, 49.9 ohm to +3V3_PHY, centre taps, shield
    for jack, sup, lines in (("J401", "+3V3_TXRX1", (("53", "1"), ("52", "2"), ("55", "3"), ("54", "6"))),
                             ("J402", "+3V3_TXRX2", (("62", "1"), ("63", "2"), ("60", "3"), ("61", "6")))):
        for chip, jp in lines:
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        want(rt, "1", "+24V_IO"); want(rt, "2", sense)
        want(jp, "1", "+24V_IO"); want(jp, "2", com); want(jp, "3", "0V_IO")
    # ---- 6 MPG
    same(("U301", stm["PB4"]), ("U602", "5"), "MPG_A"); same(("U301", stm["PB5"]), ("U602", "6"), "MPG_B")
    same(("U301", stm["PD2"]), ("U602", "3"), "RELAY_OE")
    for chip, jack in (("2", "3"), ("1", "4"), ("6", "5"), ("7", "6")):
        same(("U601", chip), ("J601", jack), f"receiver input {chip}")
    same(("U601", "3"), ("U602", "12"), "ENC_A_R"); same(("U601", "5"), ("U602", "11"), "ENC_B_R")
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            fail(f"{rn}: not on +24V_IO")
            bad[0] += 1
    # ---- 8 analog
    for esc, pin_in, mcu in (("DAC_SCK", "3", "PB13"), ("DAC_MOSI", "4", "PB15"), ("DAC_CS", "5", "PB12"), ("AO_CLAMP", "6", "PB14")):
        same(("U301", stm[mcu]), ("U801", pin_in), esc)
    same(("U801", "14"), ("U802", "3"), "SCK to the DAC"); same(("U801", "13"), ("U802", "4"), "SDI to the DAC"); same(("U801", "12"), ("U802", "2"), "CS to the DAC")
    same(("U801", "11"), ("Q801", "5"), "clamp gate"); same(("U801", "11"), ("Q801", "2"), "clamp gate 2")
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
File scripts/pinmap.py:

#!/usr/bin/env python3
"""Single source of truth for the STM32F405VGT6 pin map (docs/plan.md, MCU sheet table).

Used by relayout_symbols.py (symbol layout), build_schematics.py (net labels) and
check_pinmap.py (verifies the schematic netlist against docs/plan.md itself).

GROUPS: (side, title, [(net, pin name), ...]) in display order, top to bottom.
Nets that cross to other sheets keep the same name as the hierarchical label.
"""

LEFT_RIGHT = [
    ("left", "Reset and boot", [("NRST", "NRST"), ("BOOT0", "BOOT0")]),
    ("left", "Clock", [("CLK_MCU", "PH0"), ("PH1_TP", "PH1")]),
    ("left", "MPG encoder", [("MPG_A", "PB4"), ("MPG_B", "PB5")]),
    ("left", "EtherCAT in", [("ESC_IRQ", "PC4"), ("ESC_SYNC0", "PA0"), ("ESC_SYNC1", "PC13")]),
    ("left", "DI1-8", [(f"DI{i + 1}", p) for i, p in enumerate(["PC0", "PC1", "PC2", "PC3", "PC6", "PC7", "PC8", "PC9"])]),
    ("left", "SEL1-12", [(f"SEL{i + 1}", p) for i, p in enumerate(
        ["PB0", "PB1", "PB2", "PB8", "PB9", "PB10", "PB11", "PA15", "PB6", "PB7", "PC14", "PC15"])]),
    ("left", "Free for future use (port E)", [(f"FREE_PE{i}", f"PE{i}") for i in range(16)]),
    ("right", "DO1-8", [(f"DO{i + 1}", p) for i, p in enumerate(["PA8", "PA9", "PA10", "PA11", "PA12", "PC10", "PC11", "PC12"])]),
    ("right", "Relay enable", [("RELAY_OE", "PD2")]),
    ("right", "LEDs", [("HB_LED", "PA1"), ("ERR_LED", "PD3")]),
    ("right", "LAN9252 SPI1", [("ESC_CS", "PA4"), ("ESC_SCK", "PA5"), ("ESC_MISO", "PA6"), ("ESC_MOSI", "PA7")]),
    ("right", "LAN9252 reset", [("ESC_RST", "PC5")]),
    ("right", "DAC SPI2", [("DAC_CS", "PB12"), ("DAC_SCK", "PB13"), ("DAC_MOSI", "PB15")]),
    ("right", "Analog clamp", [("AO_CLAMP", "PB14")]),
    ("right", "Debug", [("SWDIO", "PA13"), ("SWCLK", "PA14"), ("SWO", "PB3")]),
    ("right", "UART2", [("UART2_TX", "PA2"), ("UART2_RX", "PA3")]),
    ("right", "Free for future use (port D)", [(f"FREE_PD{i}", f"PD{i}") for i in [0, 1] + list(range(4, 16))]),
]

# A part hangs beside these pins on the sheet, so the symbol leaves blank rows: a pull-down or capacitor
# hangs BELOW its pin (gap after), a pull-up hangs ABOVE it (gap before).
GAP_ROWS = 4
GAP_AFTER = {"NRST", "BOOT0", "RELAY_OE"}
GAP_BEFORE = {"ESC_RST", "AO_CLAMP"}

# Alternate function printed after the port name on the symbol
FUNCTIONS = {
    "PA4": "SPI1_NSS", "PA5": "SPI1_SCK", "PA6": "SPI1_MISO", "PA7": "SPI1_MOSI",
    "PB12": "SPI2_NSS", "PB13": "SPI2_SCK", "PB15": "SPI2_MOSI",
    "PB4": "TIM3_CH1", "PB5": "TIM3_CH2", "PC4": "EXTI4", "PA0": "EXTI0", "PC13": "EXTI13",
    "PA13": "SWDIO", "PA14": "SWCLK", "PB3": "SWO", "PA2": "USART2_TX", "PA3": "USART2_RX",
    "PH0": "OSC_IN", "PH1": "OSC_OUT", "PB2": "BOOT1", "PC14": "OSC32_IN", "PC15": "OSC32_OUT",
}

VDD_PINS = [11, 19, 28, 50, 75, 100]
VSS_PINS = [10, 27, 74, 99]

# nets that are NOT plain STM32 port signals (support circuits) are named in build_schematics.py
LAN9252_SIGNALS = ["ESC_CS", "ESC_SCK", "ESC_MISO", "ESC_MOSI", "ESC_IRQ", "ESC_SYNC0", "ESC_SYNC1", "ESC_RST"]


def all_signal_nets():
    """{net: pin name} for every port signal that is used (not 'free for future use')."""
    out = {}
    for side, title, items in LEFT_RIGHT:
        if title.startswith("Free"):
            continue
        for net, pin in items:
            out[net] = pin
    return out

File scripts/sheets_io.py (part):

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    s.wire(p1, PT.pin("1"))
    tie(s, PT.pin("2"), (1, 0), P5, "+5V_IO", 3)
    tie(s, J.pin("2"), (1, 0), GND, "0V_IO", 16)
    for pin, net in (("3", "ENC_A_P"), ("4", "ENC_A_N"), ("5", "ENC_B_P"), ("6", "ENC_B_N")):
        s.stub(J.pin(pin), (1, 0), g(6), net=net)
    note(s, "1 +5V_IO   2 0V_IO   3 A   4 A-bar   5 B   6 B-bar", g(10), g(70))

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    # ---- U601 AM26LS32A
    U = s.place("lcsc:C6180", "U601", g(150), g(60), value="AM26LS32A", lcsc="C6180",
                ref_at=(g(150), g(40)), val_at=(g(150), g(82)), justify="center")
    for pin, net in (("2", "ENC_A_P"), ("1", "ENC_A_N"), ("6", "ENC_B_P"), ("7", "ENC_B_N")):
        s.stub(U.pin(pin), (-1, 0), g(6), net=net)
    tie_bar(s, [U.pin(n) for n in ("10", "9", "14", "15")], (-1, 0), GND, "0V_IO", 4)         # unused receivers 3 and 4
    tie_bar(s, [U.pin("16"), U.pin("4")], (1, 0), P5, "+5V_IO", 4)                              # VCC, G (active high) = enabled
    tie_bar(s, [U.pin("12"), U.pin("8")], (1, 0), GND, "0V_IO", 4)                              # ~G low, GND
    s.stub(U.pin("3"), (1, 0), g(6), net="ENC_A_R")
    s.stub(U.pin("5"), (1, 0), g(6), net="ENC_B_R")
    s.no_connect(*U.pin("11")); s.no_connect(*U.pin("13"))
    decap(s, g(172), g(88), P5, "+5V_IO", GND, "0V_IO", "C601")

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    I = s.place("lcsc:C5347249", "U602", ux, uy, value="CA-IS3742LN", lcsc="C5347249",
                ref_at=(ux - g(2), uy - g(20)), val_at=(ux + g(2), uy - g(20)), justify="right", val_justify="left")
    tie_bar(s, [I.pin("16"), I.pin("10")], (-1, 0), P5, "+5V_IO", 4)
    s.stub(I.pin("12"), (-1, 0), g(6), net="ENC_A_R")
    s.stub(I.pin("11"), (-1, 0), g(6), net="ENC_B_R")
    e = s.stub(I.pin("14"), (-1, 0), g(6))
    s.hlabel("OE_FIELD", "output", e[0], e[1], 180)
    s.no_connect(*I.pin("13"))
    tie_bar(s, [I.pin("15"), I.pin("9")], (-1, 0), GND, "0V_IO", 4)
    tie_bar(s, [I.pin("1"), I.pin("7")], (1, 0), P33, "+3V3", 4)
    for pin, name, shape in (("5", "MPG_A", "output"), ("6", "MPG_B", "output"), ("3", "RELAY_OE", "input")):
        e = s.stub(I.pin(pin), (1, 0), g(10))
        s.hlabel(name, shape, e[0], e[1], 0)
    tie(s, I.pin("4"), (1, 0), GND, "GND_L", 4)                                                  # spare channel input tied low
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        tie(s, U.pin("16"), (1, 0), P5, "+5V_IO", 4)
        e = s.stub(U.pin("10"), (1, 0), g(8))
        if n == 0:
            s.hlabel("OE_FIELD", "input", e[0], e[1], 0)
        else:
            s.label("OE_FIELD", e[0], e[1], 0)
        tie_bar(s, [U.pin("15"), U.pin("9")], (1, 0), GND, "0V_IO", 4)
        for k in range(4):
            s.stub(U.pin(str(14 - k)), (1, 0), g(6), net=f"IN{4 * n + k + 1}")
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    s.no_connect(*U.pin("7"))
    tie_bar(s, [U.pin("2"), U.pin("8")], (-1, 0), GND, "GND_L", 4)
    tie_bar(s, [U.pin("16"), U.pin("10")], (1, 0), P5, A5, 4)                                   # VDDB and ENB (enabled)
    tie_bar(s, [U.pin("15"), U.pin("9")], (1, 0), GNDA, AGND, 4)
    decap(s, ux - g(26), uy - g(30), P33, "+3V3", GND, "GND_L", "C801")
    decap(s, ux + g(26), uy - g(30), P5, A5, GNDA, AGND, "C802")
    s.dashed_line(ux, g(28), ux, g(82))
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    D = s.place("lcsc:C16040", "U802", dx, dy, value="MCP4822-E/SN", lcsc="C16040",
                ref_at=(dx, dy - g(18)), val_at=(dx, dy + g(10)), justify="center")
    tie(s, D.pin("1"), (-1, 0), P5, A5, 4)
    for pin, net in (("4", "SDI_A"), ("3", "SCK_A"), ("2", "CS_A")):
        s.stub(D.pin(pin), (-1, 0), g(6), net=net)
    tie(s, D.pin("5"), (-1, 0), GNDA, AGND, 4)                                                    # LDAC low: outputs update on CS rising edge
    s.stub(D.pin("8"), (1, 0), g(6), net="DAC_A")
    s.stub(D.pin("6"), (1, 0), g(6), net="DAC_B")
    tie(s, D.pin("7"), (1, 0), GNDA, AGND, 4)
    decap(s, dx + g(30), dy - g(14), P5, A5, GNDA, AGND, "C803")

    # ---- two gain stages: LM2904 units 1 and 2
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        s.wire(n, gnode)
        Rg = vpart(s, "Device:R", f"R81{ch + 3}", gnode[0], gnode[1], "10.0k 0.1%", "C95204",
                   ref_at=(gnode[0] - g(2), gnode[1] + g(2)), val_at=(gnode[0] - g(2), gnode[1] + g(4)), justify="right")
        s.power(GNDA, AGND, *Rg.pin("2"))
        # output: OUT > 100 R (inside the loop) > output node
        o1 = s.stub(out, (1, 0), g(4))
        Ro = hpart(s, "lcec:R_H", f"R81{ch + 5}", o1[0], o1[1], "100R", "C22775")
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        # TVS and 10 nF to AGND, then the terminal
        s.wire((x2, ya), (x2 + g(36), ya))
        T = vpart(s, "lcec:D_TVS_KA_V", dref, x2 + g(8), ya, "SMAJ15A", "C148216")
        s.power(GNDA, AGND, *T.pin("2"))
        C = vpart(s, "Device:C", cref, x2 + g(22), ya, "10nF", "C1589")
        s.power(GNDA, AGND, *C.pin("2"))
        J = s.place("lcsc:C441204", f"J80{ch + 1}", x2 + g(40), ya + g(1), value=f"AO{ch + 1}", lcsc="C441204",
                    ref_at=(x2 + g(44), ya - g(3)), val_at=(x2 + g(44), ya + g(5)), justify="left")
        s.wire((x2 + g(36), ya), J.pin("1"))
        tie(s, J.pin("2"), (-1, 0), GNDA, AGND, 4)
        accessory(s, f"P80{ch + 1}", "C440880", f"2-pole plug for J80{ch + 1}", g(150), g(150) + ch * g(4))
    A = s.place("lcsc:C7934", "U803", g(205), g(150), value="LM2904", lcsc="C7934", unit=3,
                ref_at=(g(205), g(143)), val_at=(g(205), g(157)), justify="center")
    tie(s, A.pin("8"), (-1, 0), P15, "+15V_A", 4)
    tie(s, A.pin("4"), (-1, 0), GNDA, AGND, 4)
    decap(s, g(185), g(140), P15, "+15V_A", GNDA, AGND, "C804")

    # ---- clamp: both op-amp + inputs to AGND while AO_CLAMP is high; 100 k keeps them at 0 V if the DAC is unpowered
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    s.wire(g1, (g1[0] - g(4), g1[1])); s.wire(g2, (g2[0] - g(4), g2[1]))
    s.wire((g1[0] - g(4), g1[1]), (g2[0] - g(4), g2[1]))
    s.stub((g2[0] - g(4), g2[1]), (-1, 0), g(4), net="CLAMP_A")
    s.stub(Q.pin("3"), (1, 0), g(6), net="AO1_P")
    s.stub(Q.pin("6"), (1, 0), g(6), net="AO2_P")
    tie_bar(s, [Q.pin("4"), Q.pin("1")], (1, 0), GNDA, AGND, 4)
    for k, (tag, y) in enumerate((("AO1_P", g(130)), ("AO2_P", g(146)))):
        Rp = vpart(s, "Device:R", f"R82{k + 1}", g(175), y, "100k", "C25803")
        s.wire((g(175) - g(10), y), (g(175), y))
        s.label(tag, g(175) - g(10), y, 180)
        s.power(GNDA, AGND, *Rp.pin("2"))

    # ---- 5 V supply for the DAC
    lx, ly = g(60), g(135)
    L = s.place("lcsc:C42738", "U804", lx, ly, value="L78L05", lcsc="C42738", ref_at=(lx, ly - g(8)), val_at=(lx, ly + g(8)), justify="center")
    tie(s, L.pin("3"), (-1, 0), P15, "+15V_A", 6)
    tie(s, L.pin("2"), (-1, 0), GNDA, AGND, 4)
    e = s.stub(L.pin("1"), (1, 0), g(6)); s.power(P5, A5, *e)
    decap(s, lx - g(26), ly - g(2), P15, "+15V_A", GNDA, AGND, "C807", "1uF", "C559769")
    decap(s, lx + g(22), ly - g(2), P5, A5, GNDA, AGND, "C808", "1uF", "C559769")
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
